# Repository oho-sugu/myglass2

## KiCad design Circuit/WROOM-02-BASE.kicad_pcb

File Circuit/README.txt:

This Project based on http://monomake.blogspot.com/2015/08/esp-wroom-02.html

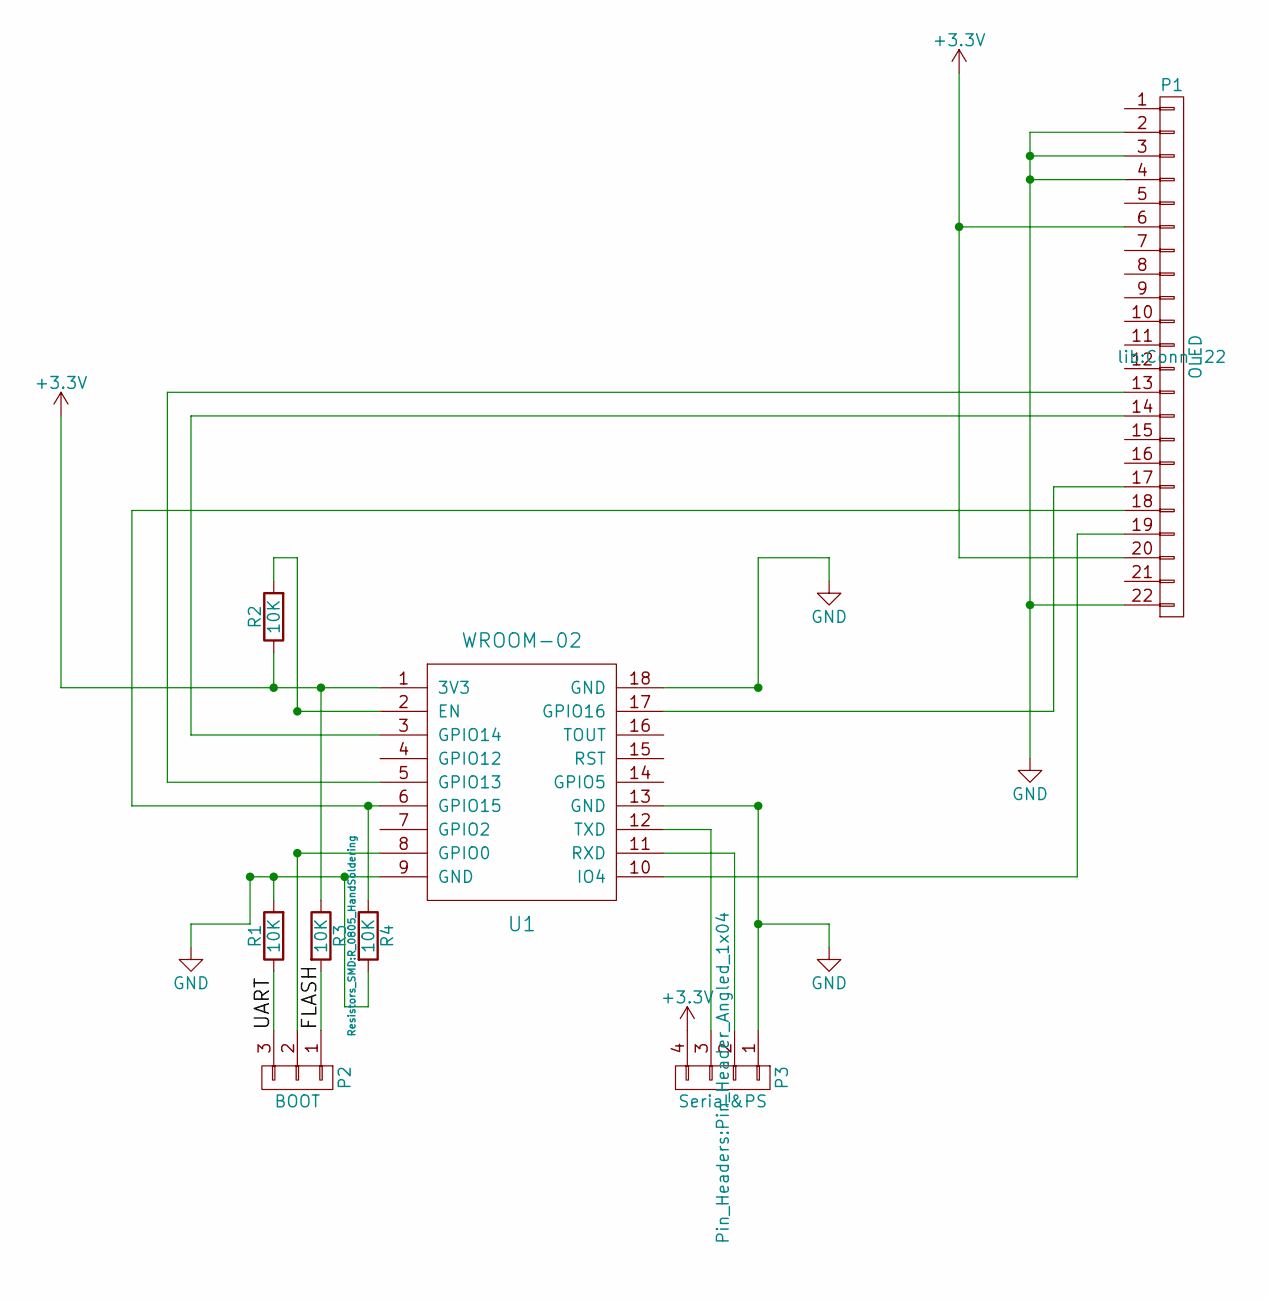
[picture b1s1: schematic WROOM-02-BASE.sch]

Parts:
P1: OLED; Conn-22
P2: BOOT; Pin_Header_Straight_1x03
P3: Serial&PS; Pin_Header_Angled_1x04
R1, R2, R3, R4: 10K; R_0805_HandSoldering
U1: WROOM-02

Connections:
+3V3: P1.6, P1.20, P3.4, R2.1, R3.1, U1.1 (3V3)
/FLASH: P2.1, R3.2
/UART: P2.3, R1.1
GND: P1.2, P1.3, P1.4, P1.22, P3.1, R1.2, R4.2, U1.9 (GND), U1.13 (GND), U1.18 (GND)
unnamed: P1.13, U1.5 (GPIO13)
unnamed: P1.14, U1.3 (GPIO14)
unnamed: P1.17, U1.17 (GPIO16)
unnamed: P1.18, R4.1, U1.6 (GPIO15)
unnamed: P1.19, U1.10 (IO4)
unnamed: P2.2, U1.8 (GPIO0)
unnamed: P3.2, U1.11 (RXD)
unnamed: P3.3, U1.12 (TXD)
unnamed: R2.2, U1.2 (EN)

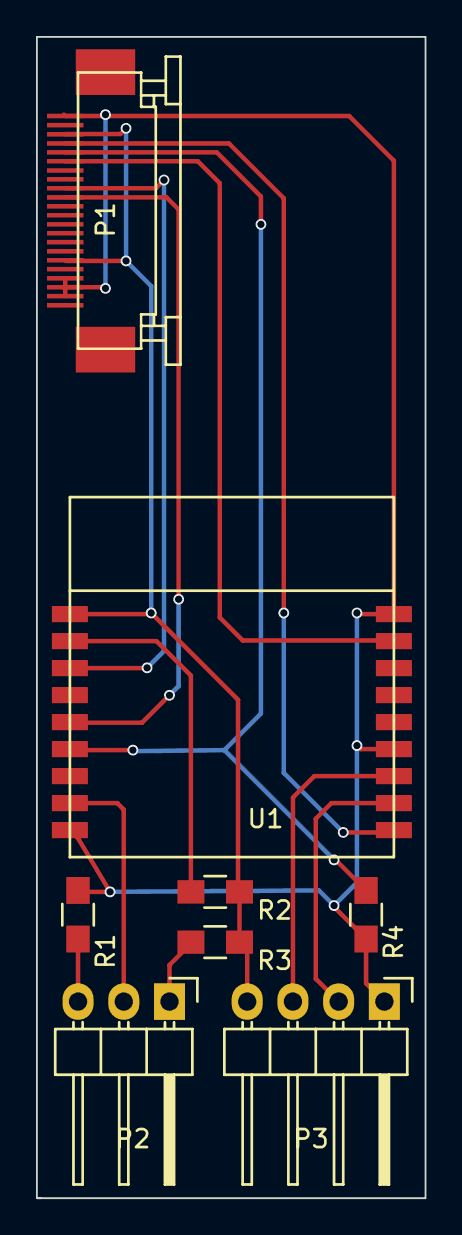
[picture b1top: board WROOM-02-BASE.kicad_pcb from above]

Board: 2 copper layers, 21.6 x 64.5 mm, 8 parts (0 on the bottom side), 13 nets.
